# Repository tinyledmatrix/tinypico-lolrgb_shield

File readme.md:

[Buy a LOL RGB Shield](https://unexpectedmaker.com/shop/tinypico-shield-lolrgb)

## 5*14 RGB-LED shield for tinypico esp-32 board
# General
* for use with tinypico esp32 board
	* https://www.tinypico.com/
	* https://github.com/tinypico 
	* [Buy a TinyPICO](https://unexpectedmaker.com/shop/tinypico-usbc)
	
* Uses 70 WS2812 LEDs in 151 package
* easy to use with fastLED
* @mcauser wrote a  MicroPython library you can find it [here](https://github.com/mcauser/micropython-tinypico-lol-rgb-shield/)
* integrated level-shifter for data signal 3,3V -> 5V
* integrated reset button (optional to use or populate) 
* connection to tinypico: 5V (supply for LEDs), GND, IO4 or IO25, reset (if switch is used)
	* with R1 or R2 user can select to use IO4 or IO25 for the led data line   
# Images 
see also folder /images

# License 
This is based on the shield template from the orignal repository. So also the licencs is shared.  
These files are released as open source under the CERN license. Please review the license before using these files in your own projects to understand your obligations.

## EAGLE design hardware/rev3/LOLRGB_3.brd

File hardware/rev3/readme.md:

# Preliminary Files for rev3

Untested! 

Changes:
* Changed Buffer to N-Fet-Buffer 
* Moved datapin to GPIO 14
	* Data-In is no more switchable via resistor 
* Power rail switch to 5V
* rev 3 uses foloowing Pins of tinyPico
	* GND (both are connected - you an use one or both)
	* 3V3 as lower voltage level for level shifter 
	+ 5V as supply voltage for LEDs 
	* GPIO14 data signal for LEDs (needs to be same voltage level as on 3.3V Pin)

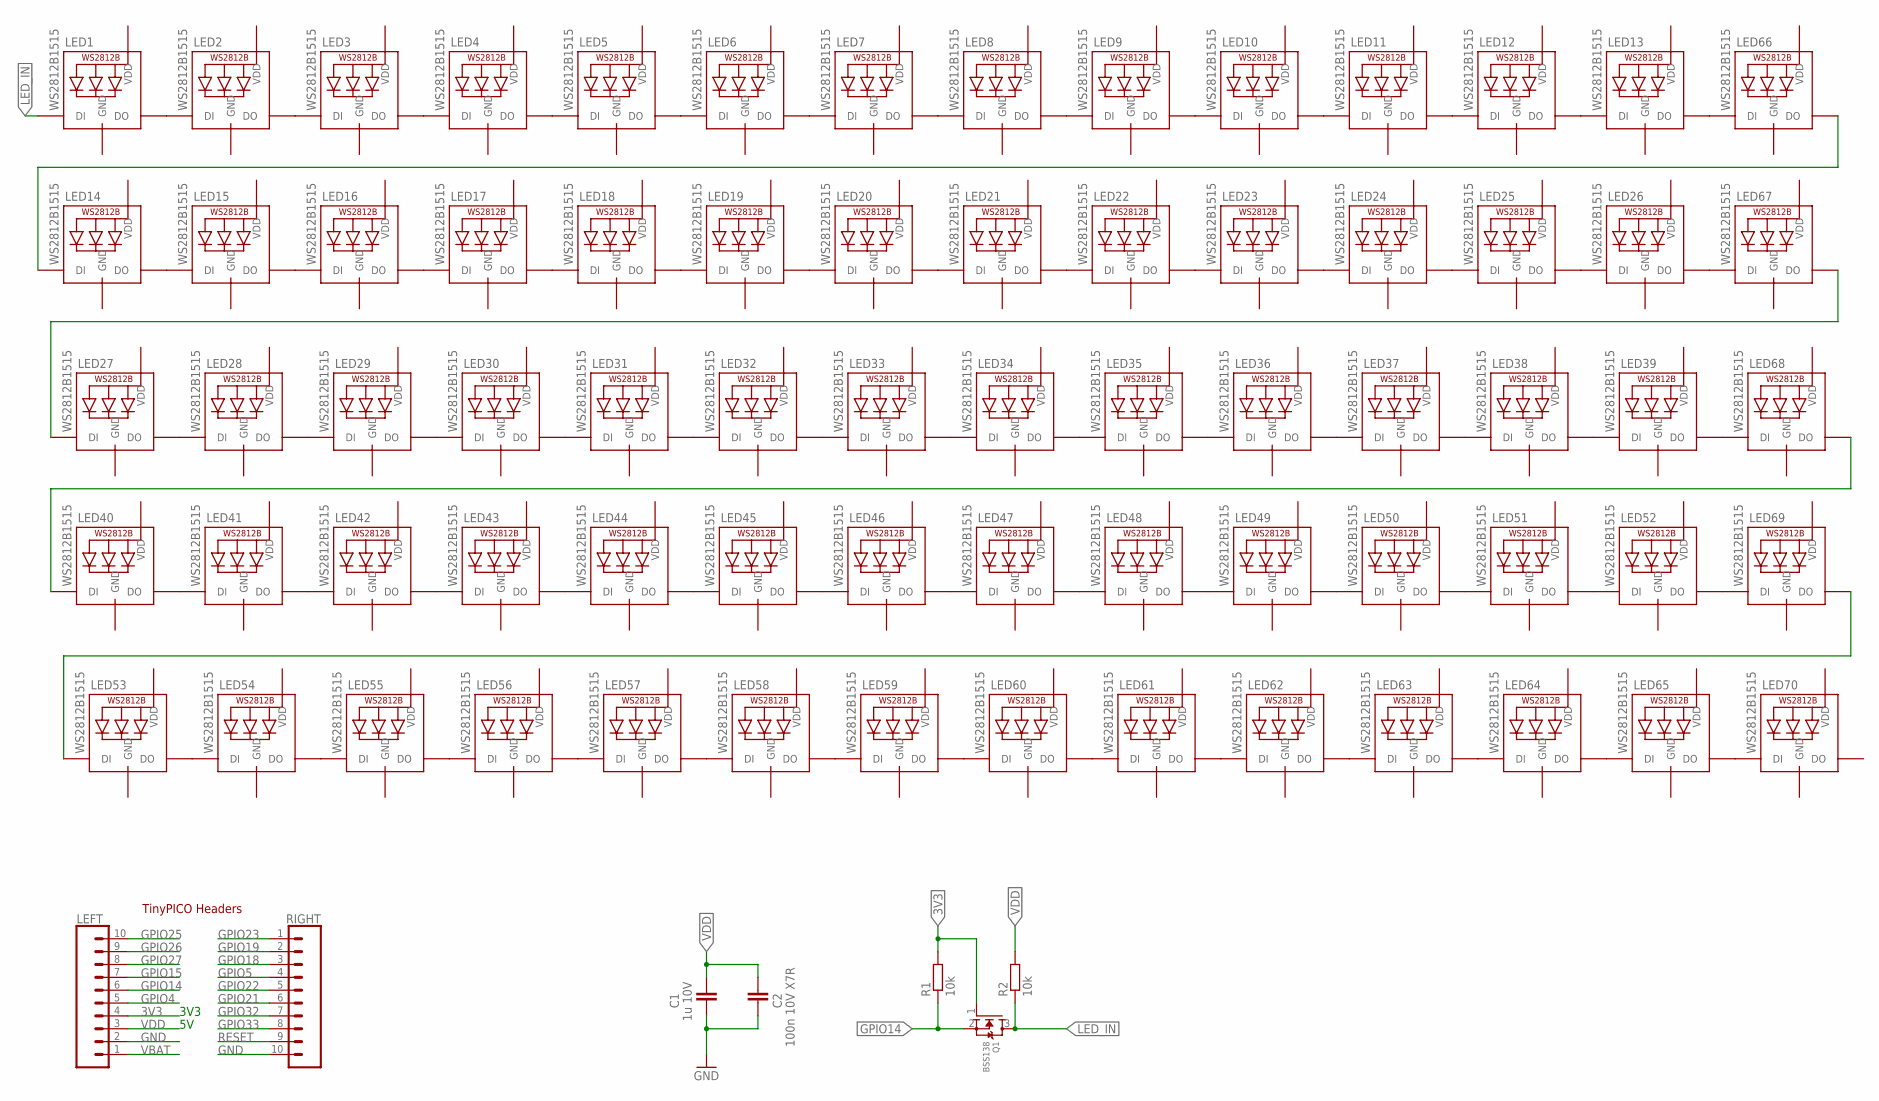
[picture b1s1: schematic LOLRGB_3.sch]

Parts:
C1: 1u 10V; C0402-VISHAY
C2: 100n 10V X7R; C0402-VISHAY
LED1, LED2, LED3, LED4, LED5, LED6, LED7, LED8, LED9, LED10, LED11, LED12, LED13, LED14, LED15, LED16, LED17, LED18, LED19, LED20, LED21, LED22, LED23, LED24, LED25, LED26, LED27, LED28, LED29, LED30, LED31, LED32, LED33, LED34, LED35, LED36, LED37, LED38, LED39, LED40, LED41, LED42, LED43, LED44, LED45, LED46, LED47, LED48, LED49, LED50, LED51, LED52, LED53, LED54, LED55, LED56, LED57, LED58, LED59, LED60, LED61, LED62, LED63, LED64, LED65, LED66, LED67, LED68, LED69, LED70: WS2812B1515; LED1515
LEFT: TINYPICO_HEADER_10NO_SILK_PTH_FEMALE; 1X10_NO_SILK
Q1: BSS138; SOT23-R
R1, R2: 10k; ADAFRUIT_R0402-VISHAY
RIGHT: TINYPICO_HEADER_10NO_SILK_PTH_FEMALE; 1X10_NO_SILK

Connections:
3V3: LEFT.4, Q1.1 (G), R1.2
GND: C1.2, C2.2, LED1.GND, LED2.GND, LED3.GND, LED4.GND, LED5.GND, LED6.GND, LED7.GND, LED8.GND, LED9.GND, LED10.GND, LED11.GND, LED12.GND, LED13.GND, LED14.GND, LED15.GND, LED16.GND, LED17.GND, LED18.GND, LED19.GND, LED20.GND, LED21.GND, LED22.GND, LED23.GND, LED24.GND, LED25.GND, LED26.GND, LED27.GND, LED28.GND, LED29.GND, LED30.GND, LED31.GND, LED32.GND, LED33.GND, LED34.GND, LED35.GND, LED36.GND, LED37.GND, LED38.GND, LED39.GND, LED40.GND, LED41.GND, LED42.GND, LED43.GND, LED44.GND, LED45.GND, LED46.GND, LED47.GND, LED48.GND, LED49.GND, LED50.GND, LED51.GND, LED52.GND, LED53.GND, LED54.GND, LED55.GND, LED56.GND, LED57.GND, LED58.GND, LED59.GND, LED60.GND, LED61.GND, LED62.GND, LED63.GND, LED64.GND, LED65.GND, LED66.GND, LED67.GND, LED68.GND, LED69.GND, LED70.GND, LEFT.2, RIGHT.10
GPIO4: LEFT.5
GPIO5: RIGHT.4
GPIO14: LEFT.6, Q1.2 (S), R1.1
GPIO15: LEFT.7
GPIO18: RIGHT.3
GPIO19: RIGHT.2
GPIO21: RIGHT.6
GPIO22: RIGHT.5
GPIO23: RIGHT.1
GPIO25: LEFT.10
GPIO26: LEFT.9
GPIO27: LEFT.8
GPIO32: RIGHT.7
GPIO33: RIGHT.8
LED_IN: LED1.DIN (DI), Q1.3 (D), R2.1
unnamed: LED13.DOUT (DO), LED66.DIN (DI)
unnamed: LED1.DOUT (DO), LED2.DIN (DI)
unnamed: LED2.DOUT (DO), LED3.DIN (DI)
unnamed: LED3.DOUT (DO), LED4.DIN (DI)
unnamed: LED4.DOUT (DO), LED5.DIN (DI)
unnamed: LED5.DOUT (DO), LED6.DIN (DI)
unnamed: LED6.DOUT (DO), LED7.DIN (DI)
unnamed: LED7.DOUT (DO), LED8.DIN (DI)
unnamed: LED8.DOUT (DO), LED9.DIN (DI)
unnamed: LED10.DOUT (DO), LED11.DIN (DI)
unnamed: LED9.DOUT (DO), LED10.DIN (DI)
unnamed: LED11.DOUT (DO), LED12.DIN (DI)
unnamed: LED12.DOUT (DO), LED13.DIN (DI)
unnamed: LED14.DOUT (DO), LED15.DIN (DI)
unnamed: LED15.DOUT (DO), LED16.DIN (DI)
unnamed: LED16.DOUT (DO), LED17.DIN (DI)
unnamed: LED17.DOUT (DO), LED18.DIN (DI)
unnamed: LED18.DOUT (DO), LED19.DIN (DI)
unnamed: LED19.DOUT (DO), LED20.DIN (DI)
unnamed: LED20.DOUT (DO), LED21.DIN (DI)
unnamed: LED21.DOUT (DO), LED22.DIN (DI)
unnamed: LED23.DOUT (DO), LED24.DIN (DI)
unnamed: LED22.DOUT (DO), LED23.DIN (DI)
unnamed: LED24.DOUT (DO), LED25.DIN (DI)
unnamed: LED25.DOUT (DO), LED26.DIN (DI)
unnamed: LED27.DOUT (DO), LED28.DIN (DI)
unnamed: LED28.DOUT (DO), LED29.DIN (DI)
unnamed: LED29.DOUT (DO), LED30.DIN (DI)
unnamed: LED30.DOUT (DO), LED31.DIN (DI)
unnamed: LED31.DOUT (DO), LED32.DIN (DI)
unnamed: LED32.DOUT (DO), LED33.DIN (DI)
unnamed: LED33.DOUT (DO), LED34.DIN (DI)
unnamed: LED34.DOUT (DO), LED35.DIN (DI)
unnamed: LED36.DOUT (DO), LED37.DIN (DI)
unnamed: LED35.DOUT (DO), LED36.DIN (DI)
unnamed: LED37.DOUT (DO), LED38.DIN (DI)
unnamed: LED38.DOUT (DO), LED39.DIN (DI)
unnamed: LED40.DOUT (DO), LED41.DIN (DI)
unnamed: LED41.DOUT (DO), LED42.DIN (DI)
unnamed: LED42.DOUT (DO), LED43.DIN (DI)
unnamed: LED43.DOUT (DO), LED44.DIN (DI)
unnamed: LED44.DOUT (DO), LED45.DIN (DI)
unnamed: LED45.DOUT (DO), LED46.DIN (DI)
unnamed: LED46.DOUT (DO), LED47.DIN (DI)
unnamed: LED47.DOUT (DO), LED48.DIN (DI)
unnamed: LED49.DOUT (DO), LED50.DIN (DI)
unnamed: LED48.DOUT (DO), LED49.DIN (DI)
unnamed: LED50.DOUT (DO), LED51.DIN (DI)
unnamed: LED51.DOUT (DO), LED52.DIN (DI)
unnamed: LED53.DOUT (DO), LED54.DIN (DI)
unnamed: LED54.DOUT (DO), LED55.DIN (DI)
unnamed: LED55.DOUT (DO), LED56.DIN (DI)
unnamed: LED56.DOUT (DO), LED57.DIN (DI)
unnamed: LED57.DOUT (DO), LED58.DIN (DI)
unnamed: LED58.DOUT (DO), LED59.DIN (DI)
unnamed: LED59.DOUT (DO), LED60.DIN (DI)
unnamed: LED60.DOUT (DO), LED61.DIN (DI)
unnamed: LED62.DOUT (DO), LED63.DIN (DI)
unnamed: LED61.DOUT (DO), LED62.DIN (DI)
unnamed: LED63.DOUT (DO), LED64.DIN (DI)
unnamed: LED64.DOUT (DO), LED65.DIN (DI)
unnamed: LED14.DIN (DI), LED66.DOUT (DO)
unnamed: LED26.DOUT (DO), LED67.DIN (DI)
unnamed: LED39.DOUT (DO), LED68.DIN (DI)
unnamed: LED52.DOUT (DO), LED69.DIN (DI)
unnamed: LED65.DOUT (DO), LED70.DIN (DI)
unnamed: LED27.DIN (DI), LED67.DOUT (DO)
unnamed: LED40.DIN (DI), LED68.DOUT (DO)
unnamed: LED53.DIN (DI), LED69.DOUT (DO)
RESET: RIGHT.9
VBAT: LEFT.1
VDD: C1.1, C2.1, LED1.VDD, LED2.VDD, LED3.VDD, LED4.VDD, LED5.VDD, LED6.VDD, LED7.VDD, LED8.VDD, LED9.VDD, LED10.VDD, LED11.VDD, LED12.VDD, LED13.VDD, LED14.VDD, LED15.VDD, LED16.VDD, LED17.VDD, LED18.VDD, LED19.VDD, LED20.VDD, LED21.VDD, LED22.VDD, LED23.VDD, LED24.VDD, LED25.VDD, LED26.VDD, LED27.VDD, LED28.VDD, LED29.VDD, LED30.VDD, LED31.VDD, LED32.VDD, LED33.VDD, LED34.VDD, LED35.VDD, LED36.VDD, LED37.VDD, LED38.VDD, LED39.VDD, LED40.VDD, LED41.VDD, LED42.VDD, LED43.VDD, LED44.VDD, LED45.VDD, LED46.VDD, LED47.VDD, LED48.VDD, LED49.VDD, LED50.VDD, LED51.VDD, LED52.VDD, LED53.VDD, LED54.VDD, LED55.VDD, LED56.VDD, LED57.VDD, LED58.VDD, LED59.VDD, LED60.VDD, LED61.VDD, LED62.VDD, LED63.VDD, LED64.VDD, LED65.VDD, LED66.VDD, LED67.VDD, LED68.VDD, LED69.VDD, LED70.VDD, LEFT.3, R2.2

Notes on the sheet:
TinyPICO Headers
3V3

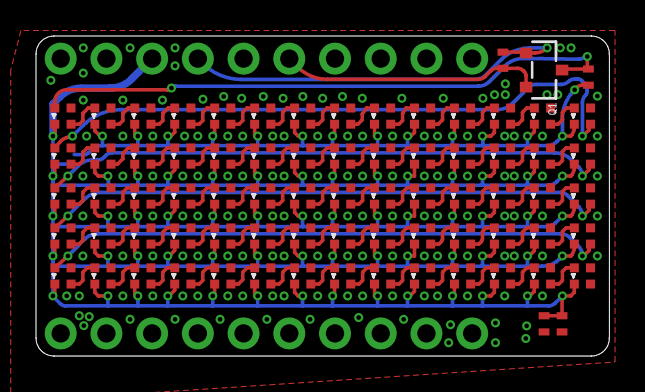
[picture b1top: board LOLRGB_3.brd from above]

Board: 2 copper layers, 31.9 x 17.8 mm, 77 parts (0 on the bottom side), 74 nets.

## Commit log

2019-09-15 Create readme.md
    created readme
2019-09-15 Created folder with images
2019-09-15 updated image readme
2019-09-15 added hw-files
2019-09-26 BOM.sheet with order Informations created
2019-10-26 added HW rev2
    Files for second rev. See rev2 readme/changelog for more details
2019-10-26 Update readme.md
    fixed typos/formation
2019-10-27 added rev3
2019-10-29 SOT23-Footprint changed
2021-02-03 Update readme.md
    Minor typo fix
